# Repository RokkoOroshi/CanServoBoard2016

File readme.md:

# CAN Servo Driver Board

can通信機能対応サーボ制御基板

## License

- MIT

## 使用ライブラリ等

- Adafruit-PWM-Servo-Driver-Library : BSD : https://github.com/adafruit/Adafruit-PWM-Servo-Driver-Library
- CAN_BUS_Shield : MIT : https://github.com/Seeed-Studio/CAN_BUS_Shield
- MsTimer2 : LGPL : http://playground.arduino.cc/Main/MsTimer2
- pins_arduino.h : LGPL
- Arduino-SerialCommand : ? : https://github.com/kroimon/Arduino-SerialCommand

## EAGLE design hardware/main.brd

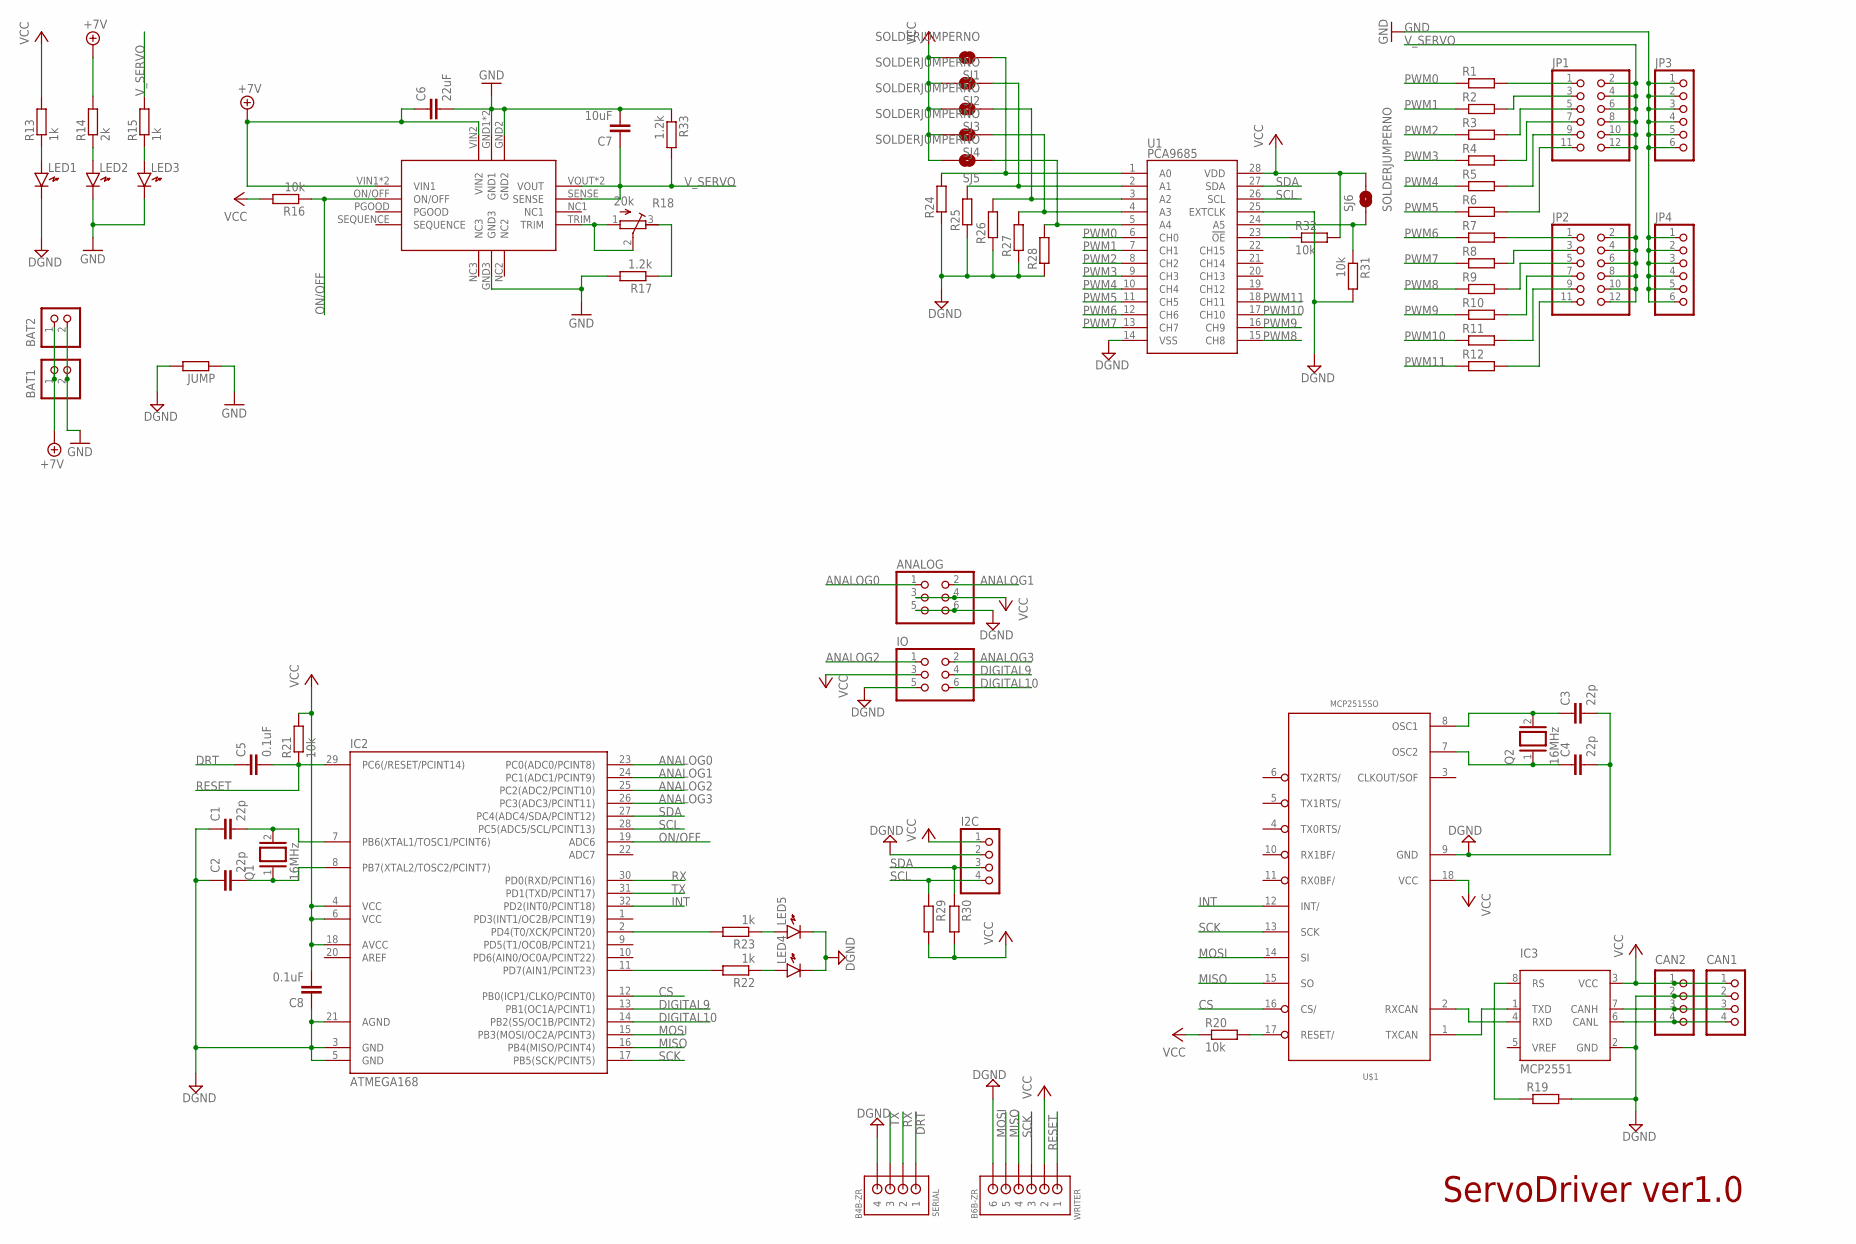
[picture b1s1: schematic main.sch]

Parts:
ANALOG: PINHD-2X3; 2X03
BAT1, BAT2: B2P-VH
C1, C2, C3, C4: 22p; C2012
C5, C8: 0.1uF; C2012
C6: 22uF; C2012
C7: 10uF; C2012
CAN1, CAN2: B4B-PH-K-S
I2C: PINHD-1X4; 1X04
IC1: OKL-T
IC2: ATMEGA168; TQFP32-08
IC3: MCP2551; SOIC
IO: PINHD-2X3; 2X03
JP1, JP2: PINHD-2X6; 2X06
JP3, JP4: PINHD-1X6; 1X06
JUMP: R-EU_M2012; M2012
LED1, LED2, LED3, LED4, LED5: LED2012
Q1, Q2: 16MHz; QS
R1, R2, R3, R4, R5, R6, R7, R8, R9, R10, R11, R12, R19, R24, R25, R26, R27, R28, R29, R30: R-EU_M2012; M2012
R13, R15, R22, R23: 1k; M2012
R14: 2k; M2012
R16, R20, R21, R31, R32: 10k; M2012
R17, R33: 1.2k; M2012
R18: 20k; RTRIM64W
SERIAL: B4B-ZR
SJ1, SJ2, SJ3, SJ4, SJ5, SJ6: SOLDERJUMPERNO; SJ_2S-NO
U1: PCA9685; TSSOP-28_4MM
U$1: MCP2515SO; SO18L
WRITER: B6B-ZR

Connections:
+7V: BAT1.1, BAT2.1, C6.1, IC1.VIN1, IC1.VIN2, IC1.VIN_BRIDGE (VIN1), R14.2
ANALOG0: ANALOG.1, IC2.23 (PC0(ADC0/PCINT8))
ANALOG1: ANALOG.2, IC2.24 (PC1(ADC1/PCINT9))
ANALOG2: IC2.25 (PC2(ADC2/PCINT10)), IO.1
ANALOG3: IC2.26 (PC3(ADC3/PCINT11)), IO.2
CS: IC2.12 (PB0(ICP1/CLKO/PCINT0)), U$1.16 (CS/)
DGND: ANALOG.5, ANALOG.6, C1.1, C2.1, C3.2, C4.2, C8.1, CAN1.2, CAN2.2, I2C.2, IC2.3 (GND), IC2.5 (GND), IC2.21 (AGND), IC3.2 (GND), IO.5, JUMP.2, LED1.K, LED4.K, LED5.K, R19.2, R24.1, R25.1, R26.1, R27.1, R28.1, R31.2, SERIAL.4, U1.14 (VSS), U1.25 (EXTCLK), U$1.9 (GND), WRITER.6
DIGITAL9: IC2.13 (PB1(OC1A/PCINT1)), IO.4
DIGITAL10: IC2.14 (PB2(SS/OC1B/PCINT2)), IO.6
DRT: C5.1, SERIAL.1
GND: BAT1.2, BAT2.2, C6.2, C7.2, IC1.GND1, IC1.GND2, IC1.GND3, IC1.GND_BRIDGE (GND1), JP3.1, JP3.2, JP3.3, JP3.4, JP3.5, JP3.6, JP4.1, JP4.2, JP4.3, JP4.4, JP4.5, JP4.6, JUMP.1, LED2.K, LED3.K, R17.2, R33.1
INT: IC2.32 (PD2(INT0/PCINT18)), U$1.12 (INT/)
MISO: IC2.16 (PB4(MISO/PCINT4)), U$1.15 (SO), WRITER.4
MOSI: IC2.15 (PB3(MOSI/OC2A/PCINT3)), U$1.14 (SI), WRITER.5
unnamed: JP1.1, R1.2
unnamed: JP1.3, R2.2
unnamed: JP1.5, R3.2
unnamed: JP1.7, R4.2
unnamed: JP1.9, R5.2
unnamed: JP1.11, R6.2
unnamed: JP2.1, R7.2
unnamed: JP2.3, R8.2
unnamed: JP2.5, R9.2
unnamed: JP2.7, R10.2
unnamed: JP2.9, R11.2
unnamed: JP2.11, R12.2
unnamed: LED1.A, R13.1
unnamed: LED2.A, R14.1
unnamed: LED3.A, R15.1
unnamed: IC1.TRIM, R18.1 (A), R18.2 (S)
unnamed: R17.1, R18.3 (E)
unnamed: C2.2, IC2.8 (PB7(XTAL2/TOSC2/PCINT7)), Q1.1
unnamed: R24.2, SJ1.1, U1.1 (A0)
unnamed: C1.2, IC2.7 (PB6(XTAL1/TOSC1/PCINT6)), Q1.2
unnamed: IC3.1 (TXD), U$1.1 (TXCAN)
unnamed: IC3.4 (RXD), U$1.2 (RXCAN)
unnamed: IC3.8 (RS), R19.1
unnamed: CAN1.3, CAN2.3, IC3.7 (CANH)
unnamed: CAN1.4, CAN2.4, IC3.6 (CANL)
unnamed: C4.1, Q2.1, U$1.7 (OSC2)
unnamed: C3.1, Q2.2, U$1.8 (OSC1)
unnamed: R25.2, SJ2.1, U1.2 (A1)
unnamed: R26.2, SJ3.1, U1.3 (A2)
unnamed: R27.2, SJ4.1, U1.4 (A3)
unnamed: IC2.2 (PD4(T0/XCK/PCINT20)), R23.2
unnamed: R28.2, SJ5.1, U1.5 (A4)
unnamed: R32.1, U1.23 (!OE)
unnamed: R20.2, U$1.17 (RESET/)
unnamed: IC2.11 (PD7(AIN1/PCINT23)), R22.2
unnamed: LED4.A, R22.1
unnamed: LED5.A, R23.1
unnamed: R31.1, SJ6.1, U1.24 (A5)
ON/OFF: IC1.ON/OFF, IC2.19 (ADC6), R16.1
PWM0: R1.1, U1.6 (CH0)
PWM1: R2.1, U1.7 (CH1)
PWM2: R3.1, U1.8 (CH2)
PWM3: R4.1, U1.9 (CH3)
PWM4: R5.1, U1.10 (CH4)
PWM5: R6.1, U1.11 (CH5)
PWM6: R7.1, U1.12 (CH6)
PWM7: R8.1, U1.13 (CH7)
PWM8: R9.1, U1.15 (CH8)
PWM9: R10.1, U1.16 (CH9)
PWM10: R11.1, U1.17 (CH10)
PWM11: R12.1, U1.18 (CH11)
RESET: C5.2, IC2.29 (PC6(/RESET/PCINT14)), R21.1, WRITER.1
RX: IC2.30 (PD0(RXD/PCINT16)), SERIAL.2
SCK: IC2.17 (PB5(SCK/PCINT5)), U$1.13 (SCK), WRITER.3
SCL: I2C.4, IC2.28 (PC5(ADC5/SCL/PCINT13)), R29.1, U1.26 (SCL)
SDA: I2C.3, IC2.27 (PC4(ADC4/SDA/PCINT12)), R30.1, U1.27 (SDA)
TX: IC2.31 (PD1(TXD/PCINT17)), SERIAL.3
VCC: ANALOG.3, ANALOG.4, C8.2, CAN1.1, CAN2.1, I2C.1, IC2.4 (VCC), IC2.6 (VCC), IC2.18 (AVCC), IC3.3 (VCC), IO.3, R13.2, R16.2, R20.1, R21.2, R29.2, R30.2, R32.2, SJ1.2, SJ2.2, SJ3.2, SJ4.2, SJ5.2, SJ6.2, U1.28 (VDD), U$1.18 (VCC), WRITER.2
V_SERVO: C7.1, IC1.SENSE, IC1.VOUT, IC1.VOUT_BRIDGE (VOUT), JP1.2, JP1.4, JP1.6, JP1.8, JP1.10, JP1.12, JP2.2, JP2.4, JP2.6, JP2.8, JP2.10, JP2.12, R15.2, R33.2

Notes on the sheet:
ServoDriver ver1.0

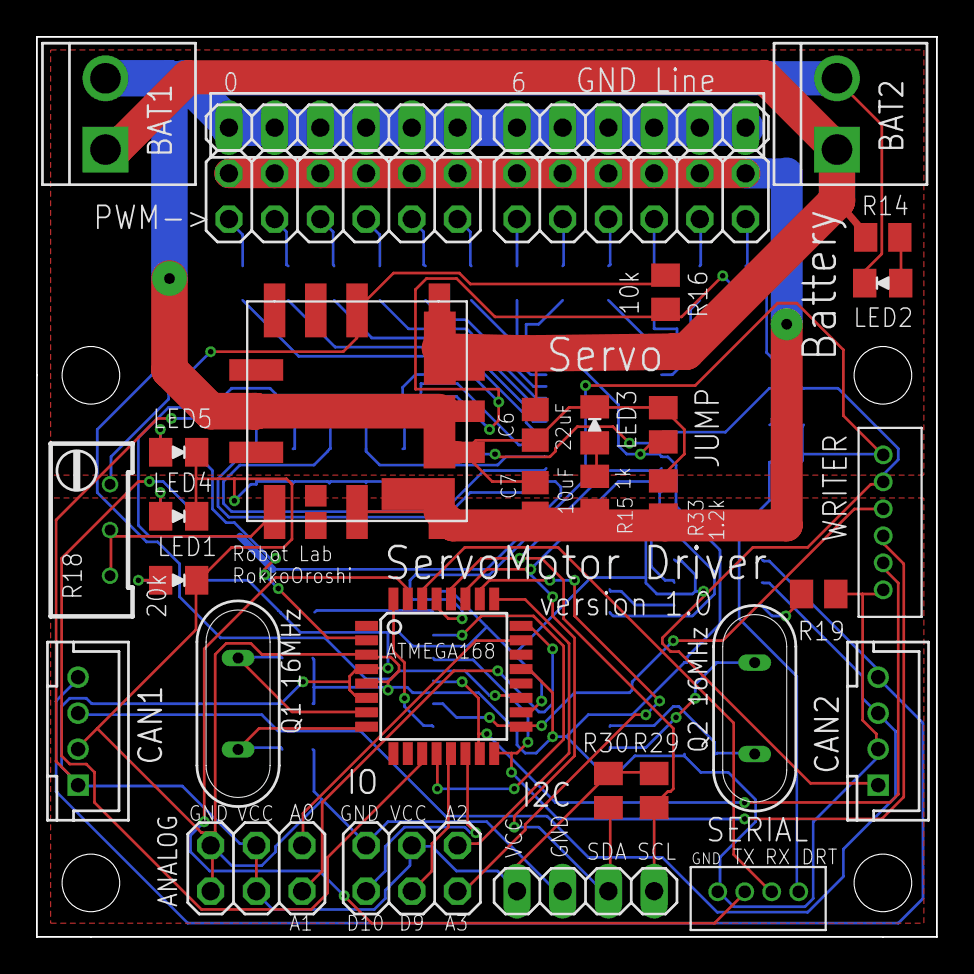
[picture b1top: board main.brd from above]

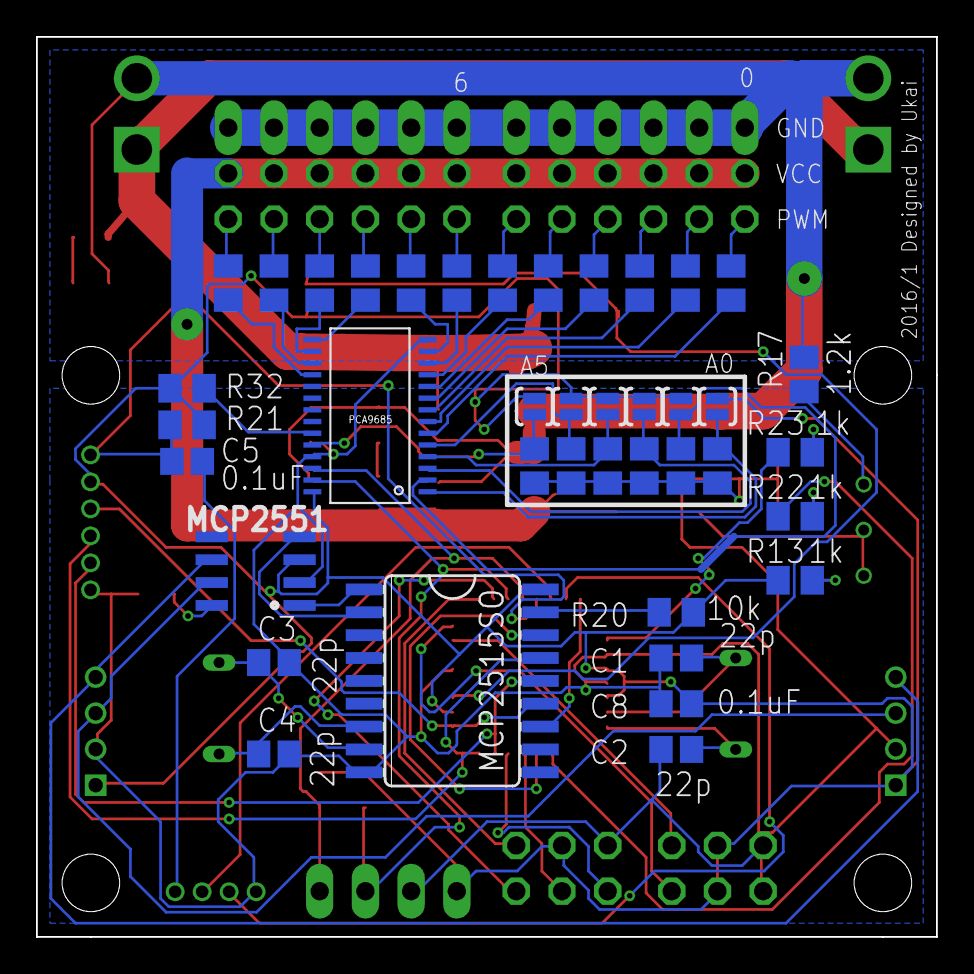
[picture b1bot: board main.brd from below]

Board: 2 copper layers, 50.0 x 50.0 mm, 73 parts (40 on the bottom side), 73 nets.

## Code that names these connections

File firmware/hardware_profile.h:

#ifndef HARDWARE_PROFILE_H
#define HARDWARE_PROFILE_H

/*
  Arduino - AVR
  ---------
  D0  - PD0
  D1  - PD1
  D2  - PD2
  D3  - PD3
  D4  - PD4
  D5  - PD5
  D6  - PD6
  D7  - PD7
  ---------
  D8  - PB0
  D9  - PB1
  D10 - PB2
  D11 - PB3
  D12 - PB4
  D13 - PB5
  ---------
  A0  - PC0
  A1  - PC1
  A2  - PC2
  A3  - PC3
  A4  - PC4
  A5  - PC5
  (32pin Only)
  A6  - ADC6
  A7  - ADC7
 */


// Digital Pin
static const uint8_t SPI_CS   =  8;
static const uint8_t SPI_MOSI = 11;
static const uint8_t SPI_MISO = 12;
static const uint8_t SPI_SCK  = 13;

static const uint8_t CAN_INT  =  2;
static const uint8_t CAN_CS   =  8;
static const uint8_t CAN_MOSI = 11;
static const uint8_t CAN_MISO = 12;
static const uint8_t CAN_SCK  = 13;

static const uint8_t RX       =  0;
static const uint8_t TX       =  1;

static const uint8_t STAT_LED1=  4;
static const uint8_t STAT_LED2=  7;


static const uint8_t SERVO_OFF = 3;

// Analog Pin
static const uint8_t INPUT0 = 14; // A0
static const uint8_t INPUT1 = 15; // A1
static const uint8_t INPUT2 = 16; // A2
static const uint8_t INPUT3 = 17; // A3

static const uint8_t INPUT9 = 9; // D9
static const uint8_t INPUT10 = 10;// D10

static const uint8_t I2C_SDA = 18; // A4
static const uint8_t I2C_SCL = 19;  // A5

#endif

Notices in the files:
parts and their libraries:
SparkFun-DigitalIC: Licensing: Creative Commons ShareAlike 4.0 International - https://creativecommons.org/licenses/by-sa/4.0
